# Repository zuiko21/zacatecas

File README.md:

# Zacatecas
Chihuahua-based 65C02 SBC with integrated peripherals (LCD text screen, microSD card reader, 8-key pad)

## Specs

- 65C02 CPU at 1 MHz
- 32 KiB RAM
- 16 KiB ROM
- VIA 65C22 (Versatile Interface Adapter)
- 16x2 LCD text screen (HD44780-based, 4-bit parallel interface) with software-controlled backlight
- microSD card reader (_bit-banged_ SPI)
- Piezo buzzer (programmable thru VIA outputs `PB7` and `CB2`)
- Independent LED output, plus software-controlled microSD card activity LED
- _nanoLink_ input for card-less boot and development
- _SS22_ synchronous serial port (developed from a [6502.org](https://6502.org/forum/viewtopic.php?p=19484) idea by Garth Wilson and Samuel Falvo)

## Firmware

See the generic [BIOS interface](firmware/bios.md)
as well as the _specific_ [Low Level Library](firmware/lll.md) for Zacatecas.

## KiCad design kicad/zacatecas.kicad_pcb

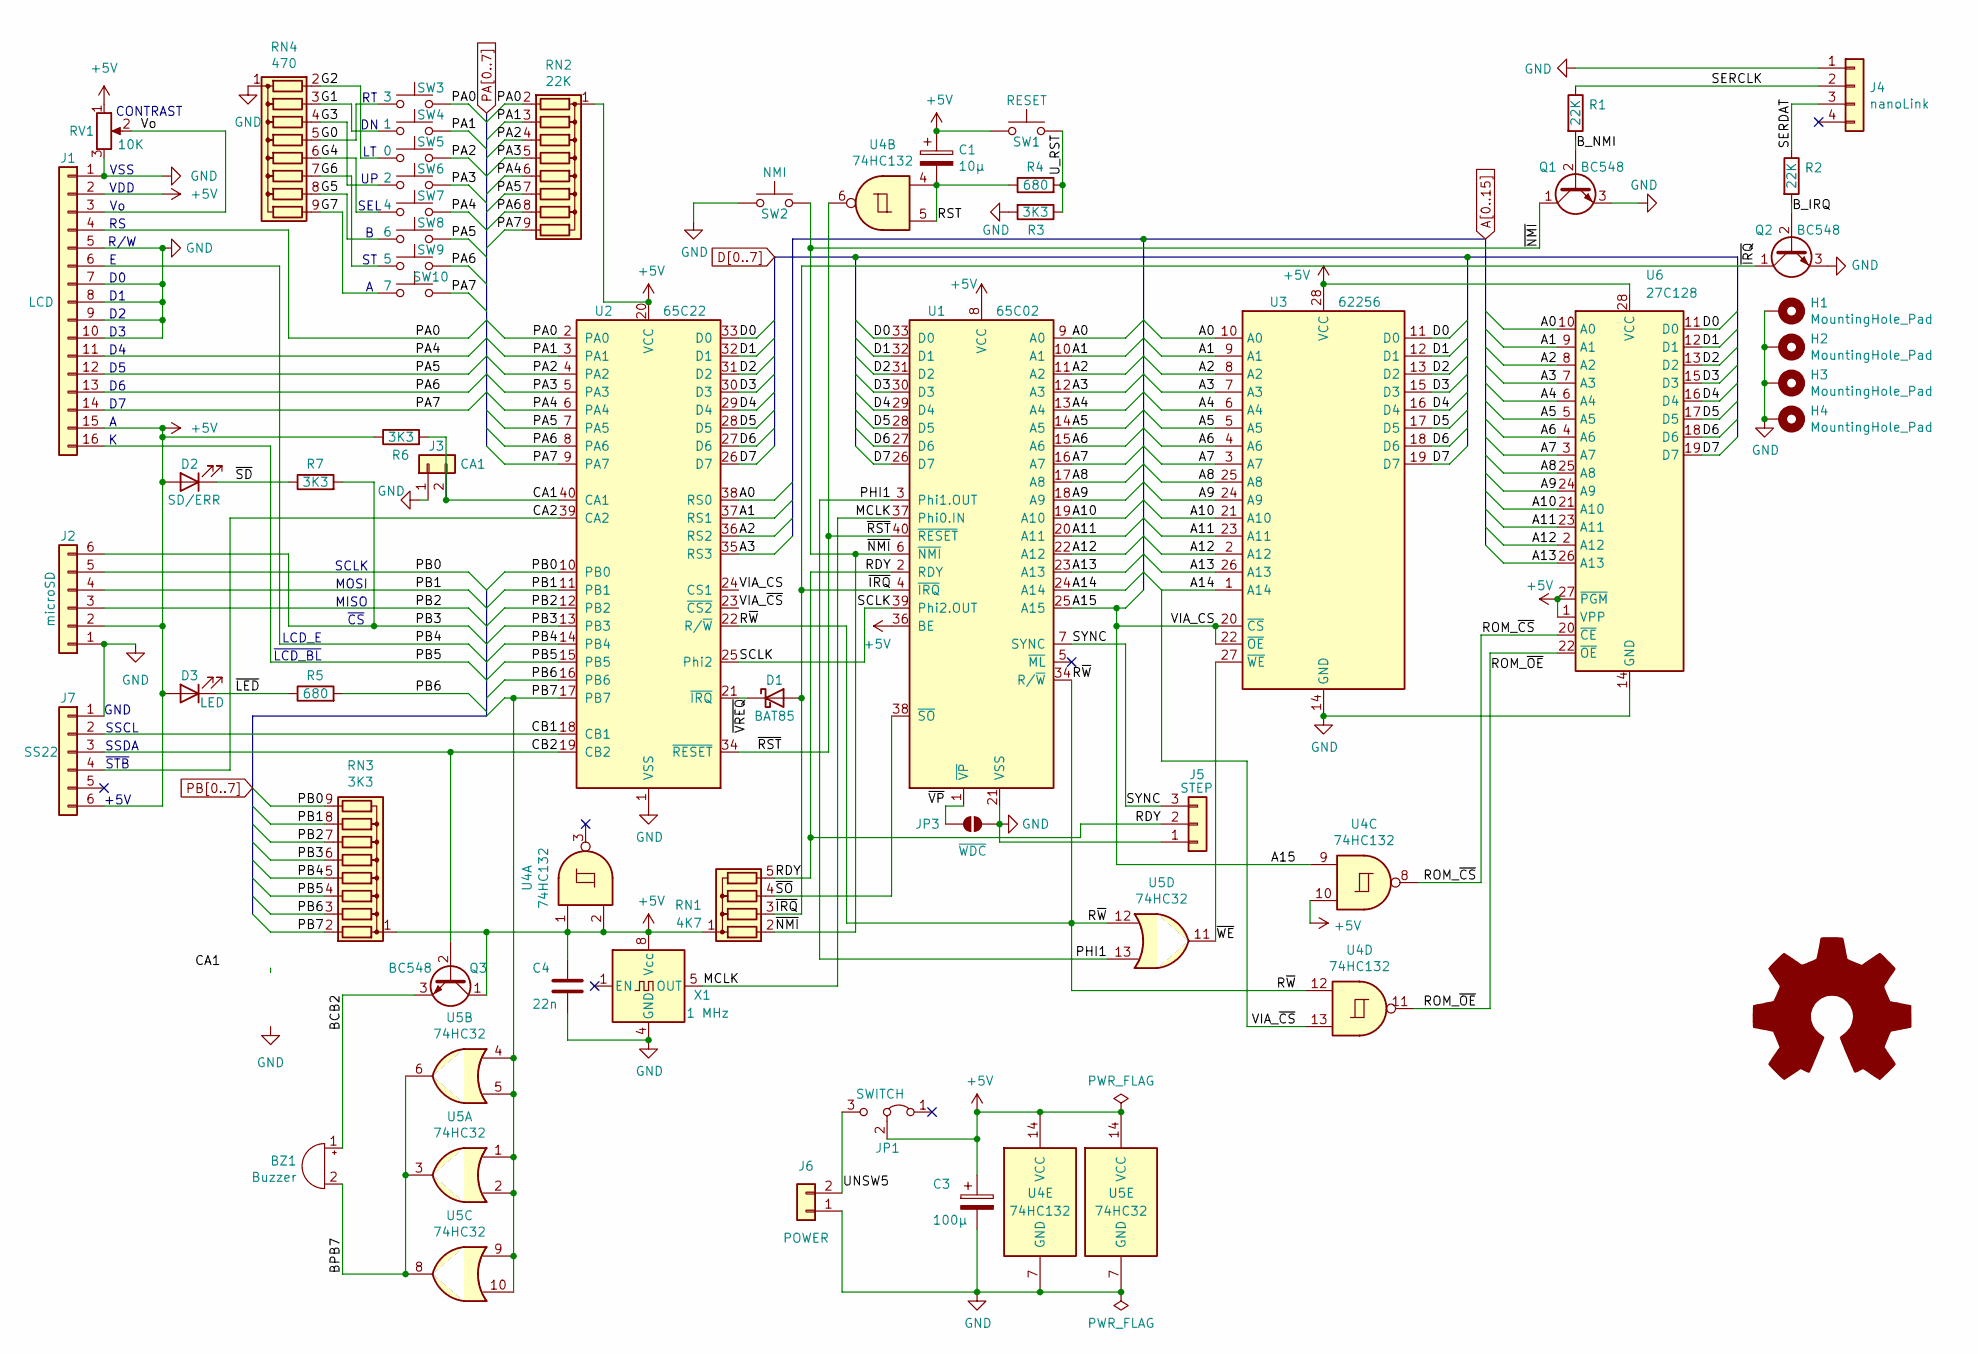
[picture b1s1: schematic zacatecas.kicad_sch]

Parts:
BZ1: Buzzer; Buzzer_12x9.5RM7.6
C1: 10µ; CP_Radial_D4.0mm_P1.50mm
C3: 100µ; CP_Radial_D4.0mm_P1.50mm
C4: 22n; C_Rect_L7.2mm_W2.5mm_P5.00mm_FKS2_FKP2_MKS2_MKP2
D1: BAT85; D_DO-35_SOD27_P2.54mm_Vertical_KathodeUp
D2: SD/ERR; LED_D3.0mm
D3: LED; LED_D3.0mm
H1, H2, H3, H4: MountingHole_Pad; MountingHole_3.2mm_M3_DIN965_Pad
J1: LCD; PinHeader_1x16_P2.54mm_Vertical
J2: microSD; PinSocket_1x06_P2.54mm_Vertical
J3: CA1; PinHeader_1x02_P2.54mm_Vertical
J4: nanoLink; PinHeader_1x04_P2.54mm_Vertical
J5: STEP; PinHeader_1x03_P2.54mm_Vertical
J6: POWER; JST_EH_S2B-EH_1x02_P2.50mm_Horizontal
J7: SS22; PinHeader_1x06_P2.54mm_Vertical
JP1: SWITCH; PowerSwitch
JP3: ~{WDC}; SolderJumper-2_P1.3mm_Open_RoundedPad1.0x1.5mm
LOGO1: Logo_Open_Hardware_Large; OSHW-Symbol_8.9x8mm_SilkScreen
Q1, Q2, Q3: BC548; TO-92_Inline
R1, R2: 22K; R_Axial_DIN0207_L6.3mm_D2.5mm_P2.54mm_Vertical
R3, R6, R7: 3K3; R_Axial_DIN0207_L6.3mm_D2.5mm_P2.54mm_Vertical
R4, R5: 680; R_Axial_DIN0207_L6.3mm_D2.5mm_P2.54mm_Vertical
RN1: 4K7; R_Array_SIP5
RN2: 22K; R_Array_SIP9
RN3: 3K3; R_Array_SIP9
RN4: 470; R_Array_SIP9
RV1: 10K; Potentiometer_Piher_PT-6-V_Vertical
SW1: RESET; SW_PUSH_6mm
SW2: NMI; SW_PUSH_6mm
SW3: 3; SW_PUSH_6mm
SW4: 1; SW_PUSH_6mm
SW5: 0; SW_PUSH_6mm
SW6: 2; SW_PUSH_6mm
SW7: 4; SW_PUSH_6mm
SW8: 6; SW_PUSH_6mm
SW9: 5; SW_PUSH_6mm
SW10: 7; SW_PUSH_6mm
U1: 65C02; DIP-40_W15.24mm_Socket
U2: 65C22; DIP-40_W15.24mm_Socket
U3: 62256; DIP-28_W15.24mm_Socket
U4: 74HC132; DIP-14_W7.62mm_Socket
U5: 74HC32; DIP-14_W7.62mm_Socket
U6: 27C128; DIP-28_W15.24mm_Socket
X1: 1 MHz; Oscillator_DIP-8

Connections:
+5V: C1.1, C3.1, C4.1, D2.2 (A), D3.2 (A), J1.2, J1.15, J2.2, J7.6, JP1.2 (C), Q3.1 (C), R6.1, RN1.1 (common), RN2.1 (common), RN3.1 (common), RV1.1, SW1.2, U1.8 (VCC), U1.36 (BE), U2.20 (VCC), U3.28 (VCC), U4.1, U4.2, U4.10, U4.14 (VCC), U5.14 (VCC), U6.1 (VPP), U6.27 (~PGM), U6.28 (VCC), X1.8 (Vcc)
/BCB2: BZ1.1 (-), Q3.3 (E)
/BPB7: BZ1.2 (+), U5.3, U5.6, U5.8
/B_IRQ: Q2.2 (B), R2.2
/B_NMI: Q1.2 (B), R1.2
/CA1: J3.2, R6.2, U2.40 (CA1)
/CA2: J7.4, U2.39 (CA2)
/CB1: J7.2, U2.18 (CB1)
/CB2: J7.3, Q3.2 (B), U2.19 (CB2)
/G0: RN4.5 (R4), SW3.1
/G1: RN4.3 (R2), SW4.1
/G2: RN4.2 (R1), SW5.1
/G3: RN4.4 (R3), SW6.1
/G4: RN4.6 (R5), SW7.1
/G5: RN4.8 (R7), SW8.1
/G6: RN4.7 (R6), SW9.1
/G7: RN4.9 (R8), SW10.1
/MCLK: U1.37 (Phi0.IN), X1.5 (OUT)
/PHI1: U1.3 (Phi1.OUT), U5.13
/RDY: J5.2, RN1.5 (R4), U1.2 (RDY)
/ROM_~CS: U4.8, U6.20 (~CE)
/ROM_~OE: U4.11, U6.22 (~OE)
/RST: C1.2, R4.1, U4.4, U4.5
/R~W: U1.34 (R/~W), U2.22 (R/~W), U4.12, U5.12
/SCLK: U1.39 (Phi2.OUT), U2.25 (Phi2)
/SERCLK: J4.2, R1.1
/SERDAT: J4.3, R2.1
/SYNC: J5.3, U1.7 (SYNC)
/UNSW5: J6.2, JP1.3 (B)
/U_RST: R3.1, R4.2, SW1.1
/Vo: J1.3, RV1.2
/~IRQ: D1.2 (A), Q2.1 (C), RN1.3 (R2), U1.4 (~IRQ)
/~LED: D3.1 (K), R5.1
/~NMI: Q1.1 (C), RN1.2 (R1), SW2.2, U1.6 (~NMI)
/~RST: U1.40 (~RESET), U2.34 (~RESET), U4.6
/~SD: D2.1 (K), R7.1
/~SO: RN1.4 (R3), U1.38 (~SO)
/~VP: JP3.1 (A), U1.1 (~VP)
/~VREQ: D1.1 (K), U2.21 (~IRQ)
/~WE: U3.27 (~WE), U5.11
A0: U1.9 (A0), U2.38 (RS0), U3.10 (A0), U6.10 (A0)
A1: U1.10 (A1), U2.37 (RS1), U3.9 (A1), U6.9 (A1)
A2: U1.11 (A2), U2.36 (RS2), U3.8 (A2), U6.8 (A2)
A3: U1.12 (A3), U2.35 (RS3), U3.7 (A3), U6.7 (A3)
A4: U1.13 (A4), U3.6 (A4), U6.6 (A4)
A5: U1.14 (A5), U3.5 (A5), U6.5 (A5)
A6: U1.15 (A6), U3.4 (A6), U6.4 (A6)
A7: U1.16 (A7), U3.3 (A7), U6.3 (A7)
A8: U1.17 (A8), U3.25 (A8), U6.25 (A8)
A9: U1.18 (A9), U3.24 (A9), U6.24 (A9)
A10: U1.19 (A10), U3.21 (A10), U6.21 (A10)
A11: U1.20 (A11), U3.23 (A11), U6.23 (A11)
A12: U1.22 (A12), U3.2 (A12), U6.2 (A12)
A13: U1.23 (A13), U3.26 (A13), U6.26 (A13)
A14: U1.24 (A14), U2.23 (~CS2), U3.1 (A14), U4.13
A15: U1.25 (A15), U2.24 (CS1), U3.20 (~CS), U3.22 (~OE), U4.9
D0: U1.33 (D0), U2.33 (D0), U3.11 (D0), U6.11 (D0)
D1: U1.32 (D1), U2.32 (D1), U3.12 (D1), U6.12 (D1)
D2: U1.31 (D2), U2.31 (D2), U3.13 (D2), U6.13 (D2)
D3: U1.30 (D3), U2.30 (D3), U3.15 (D3), U6.15 (D3)
D4: U1.29 (D4), U2.29 (D4), U3.16 (D4), U6.16 (D4)
D5: U1.28 (D5), U2.28 (D5), U3.17 (D5), U6.17 (D5)
D6: U1.27 (D6), U2.27 (D6), U3.18 (D6), U6.18 (D6)
D7: U1.26 (D7), U2.26 (D7), U3.19 (D7), U6.19 (D7)
GND: C3.2, C4.2, H1.1, H2.1, H3.1, H4.1, J1.1, J1.5, J1.7, J1.8, J1.9, J1.10, J2.1, J3.1, J4.1, J5.1, J6.1, J7.1, JP3.2 (B), Q1.3 (E), Q2.3 (E), R3.2, RN4.1 (common), RV1.3, SW2.1, U1.21 (VSS), U2.1 (VSS), U3.14 (GND), U4.7 (GND), U5.7 (GND), U6.14 (GND), X1.4 (GND)
PA0: J1.4, RN2.2 (R1), SW3.2, U2.2 (PA0)
PA1: RN2.3 (R2), SW4.2, U2.3 (PA1)
PA2: RN2.4 (R3), SW5.2, U2.4 (PA2)
PA3: RN2.5 (R4), SW6.2, U2.5 (PA3)
PA4: J1.11, RN2.6 (R5), SW7.2, U2.6 (PA4)
PA5: J1.12, RN2.7 (R6), SW8.2, U2.7 (PA5)
PA6: J1.13, RN2.8 (R7), SW9.2, U2.8 (PA6)
PA7: J1.14, RN2.9 (R8), SW10.2, U2.9 (PA7)
PB0: J2.5, RN3.9 (R8), U2.10 (PB0)
PB1: J2.4, RN3.8 (R7), U2.11 (PB1)
PB2: J2.3, RN3.7 (R6), U2.12 (PB2)
PB3: J2.6, R7.2, RN3.6 (R5), U2.13 (PB3)
PB4: J1.6, RN3.5 (R4), U2.14 (PB4)
PB5: J1.16, RN3.4 (R3), U2.15 (PB5)
PB6: R5.2, RN3.3 (R2), U2.16 (PB6)
PB7: RN3.2 (R1), U2.17 (PB7), U5.1, U5.2, U5.4, U5.5, U5.9, U5.10

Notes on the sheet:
~{LCD_BL}
VSS
MISO
SEL
SSDA
CONTRAST
SSCL
+5V
~{CS}
~{STB}
VDD
SCLK
LCD_E
GND
MOSI
R/W

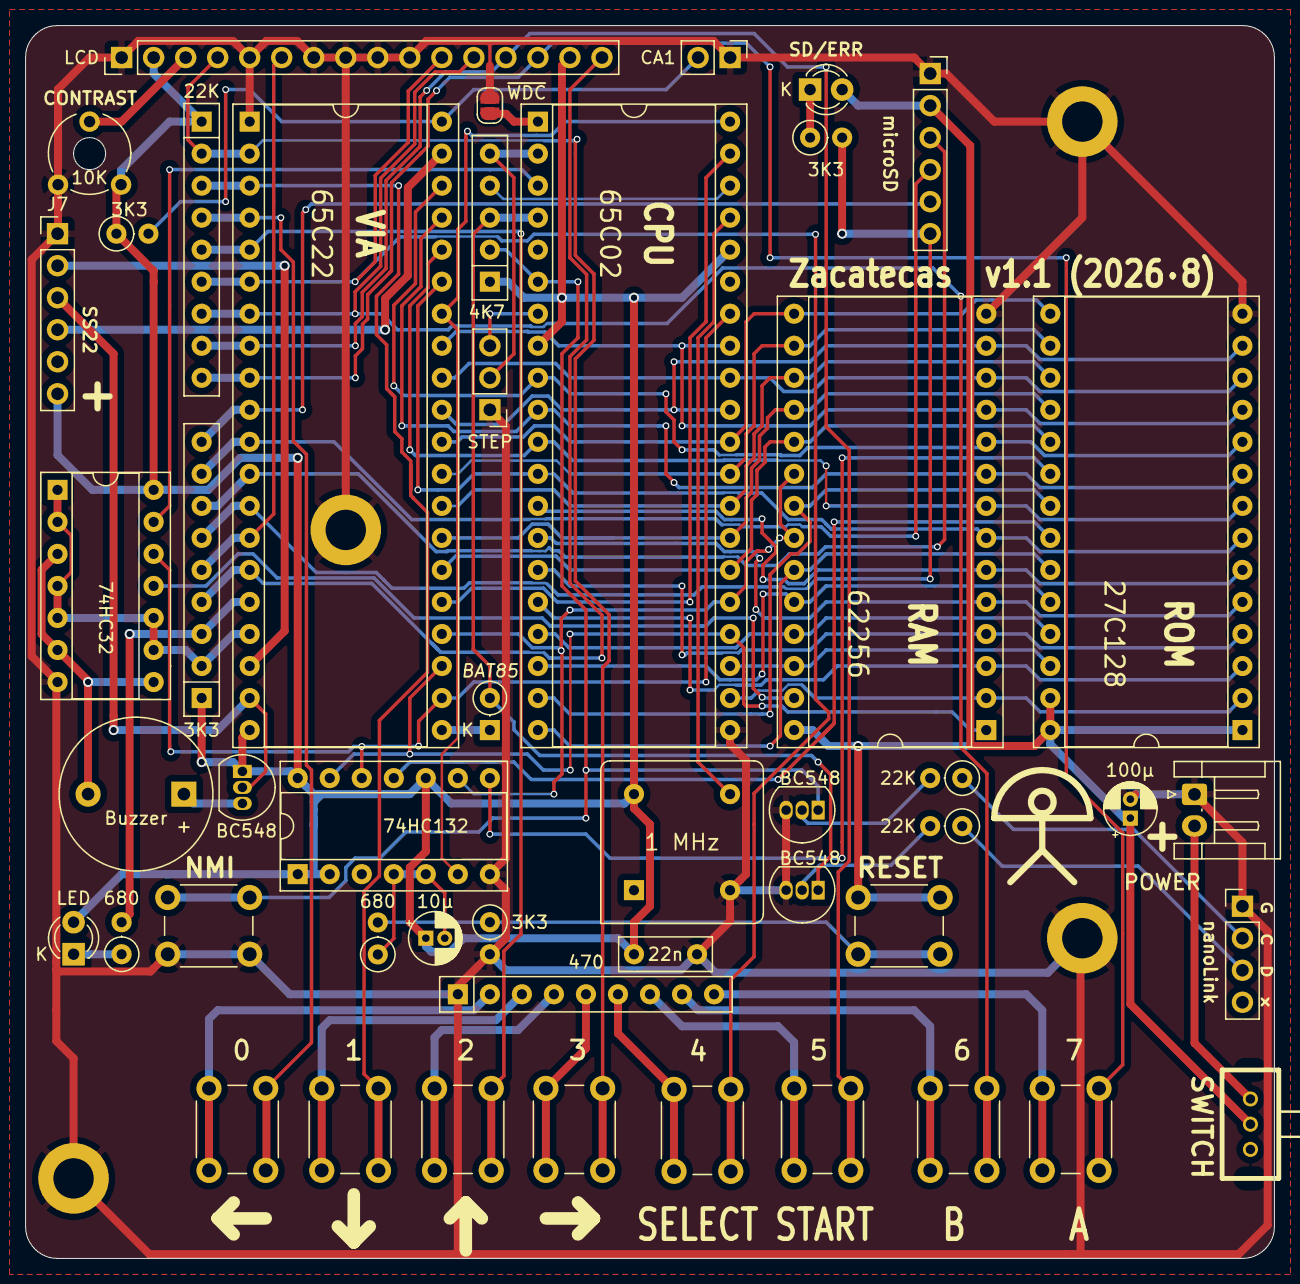
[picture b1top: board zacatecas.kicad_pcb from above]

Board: 2 copper layers, 99.1 x 97.8 mm, 53 parts (1 on the bottom side), 81 nets.

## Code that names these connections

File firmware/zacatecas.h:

; **************************************
; *** Zacatecas hardware definitions ***
; **************************************
#ifndef	SPEED
#define		SPEED	1000000
#endif

; LCD at PB4...PB5, BL is active LOW
#define		LCD_BLON	%11011111
#define		LCD_BLOFF	%00100000
#define		LCD_EN		%00010000
#define		LCD_DIS		%11101111

; LCD data at PA4...PA7, RS at PA0
#define		LCD_RS		%00000001
#define		LCD_DATA	%11110000

; SD interface at PB0...PB3, CS is active LOW
#define		SD_EN		%11110111
#define		SD_DIS		%00001000
#define		SD_MISO		%00000100
#define		SD_MOSI		%00000010
#define		SD_CLK		%00000001

; Emilio's LED at PB6, active LOW
#define		LED_ON		%10111111
#define		LED_OFF		%01000000

; key pad at PA0...PA7, all active LOW
#define		PAD_RT		%00000001
#define		PAD_DN		%00000010
#define		PAD_LT		%00000100
#define		PAD_UP		%00001000
#define		PAD_SEL		%00010000
#define		PAD_B		%00100000
#define		PAD_ST		%01000000
#define		PAD_A		%10000000

; *** VIA constants ***
#define	IORB	VIA+0
#define	IORA	VIA+1
#define	DDRB	VIA+2
#define	DDRA	VIA+3
#define	T1CL	VIA+4
#define	T1CH	VIA+5
#define	T1LL	VIA+6
#define	T1LH	VIA+7
#define	T2CL	VIA+8
#define	T2CH	VIA+9
#define	VSR		VIA+10
#define	ACR		VIA+11
#define	PCR		VIA+12
#define	IFR		VIA+13
#define	IER		VIA+14
#define	NHRA	VIA+15

; ****************************
; *** standard definitions ***
	fw_irq	= $0200
	fw_nmi	= $0202
	ticks	= $0206
	fw_cbin	= $0210			; DLE mode
	fw_ciop	= $021D			; cursor address into DDRAM (1 byte)
	fw_scur	= $0222			; flag D7=cursor ON
	gamepad	= $0226

; ****************************
; *** *** SD card BIOS *** ***
; *** mount point  *** NEW for FAT32 support($2E8-$2F1)
ds_cnt		= $2E8			; directory sector counter, unfortunately no longer in ZP ($2E8)
cnt			= ds_cnt		; *** *** DEBUG USE *** ***
sec_clus	= ds_cnt+1		; number of sectors per cluster $2E9
dir_clus	= sec_clus+1	; first cluster of directory (needed for subtract) $2EA
mnt_point	= dir_clus+4	; mount point (BIG endian like arg) $2EE..$2F1

; *** interface vectors ***
;;sd_dev_err	= $2F2			; error code for previous device, in case Fast SPI is not present
;;sd_dev_id	= $2F3			; will add 47 to display ' ' for devCart, 0...3 for Fast SPI
v_spi_tr	= $2F4
v_cs_enable	= $2F6
v_cs_disable= $2F8			; routine pointers just before tmp_siz (maybe fixed calls?)

; *** sector buffer and header pointers ***
tmp_siz		= $2FA			; $2FA-$2FB top 16 bits of temporary size for remaining free block (max. 16M)
hd_cache	= tmp_siz+2		; $2FC-$2FF current header sector position (big-endian)
buffer		= $300
magic1		= buffer+0		; must contain zero
magic2		= buffer+7		; must contain CR (13)
magic3		= buffer+255	; must contain zero (assume filesize < 16 MiB)
bootsig		= buffer+1		; must contain 'dX' for bootable ROM images, 'dA' for generic files, 'dL' for free space, 'pZ' for regular executables
fname		= buffer+8
ftime		= buffer+248	; time in MS-DOS format
fdate		= buffer+250	; date in MS-DOS format
fsize		= buffer+252	; file size INCLUDING 256-byte header
; ****************************

; ************************************
; *** Zacatecas hardware addresses ***
	VIA		= $BFF0			; EEEEEEEEEEEEEEEEEEEEEEEEEEK
	t1ct	= (SPEED/250)-2	; 250 Hz interrupt at 1 MHz (or whatever) clock rate
; ************************************

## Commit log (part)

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2026-04-18 Some basic init
2026-04-24 Runnable code in snippets.s, with ISR and ROM/RAM option
2026-04-24 add KiCAD folder
2026-04-24 add header and placeholder NMI handler
2026-04-24 Include hardware definitions
2026-04-24 fix missing labels
2026-04-24 fix no_ca1 as well
2026-04-25 Full hardware definition, new jiffy counter
2026-04-25 new jiffy, fix LCD low nybble and safer PANIC
2026-04-25 Add Emilio's LED definitions
2026-04-25 add gamepad address
2026-04-25 add gamepad read on ISR
2026-04-25 make gamepad active HIGH
2026-04-26 stub for LCD initialisation
2026-04-26 continue LCD initialisation
2026-04-26 LCD init seems OK
2026-04-27 new header type and proper interrupt mask handling by LCD
2026-04-27 add startup bong
2026-04-27 add splash string
2026-05-07 Create jump table
2026-05-07 Stub for CONIO thru BIOS jump table

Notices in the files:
kicad/zacatecas.kicad_sch:
(c) 2026 Carlos J. Santisteban
